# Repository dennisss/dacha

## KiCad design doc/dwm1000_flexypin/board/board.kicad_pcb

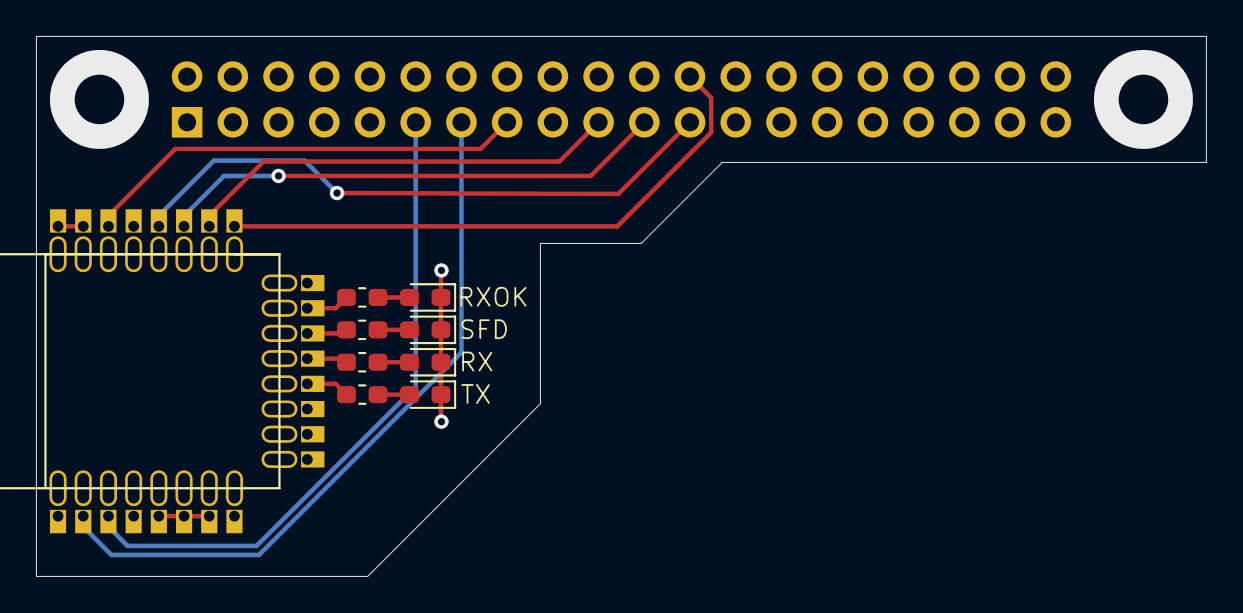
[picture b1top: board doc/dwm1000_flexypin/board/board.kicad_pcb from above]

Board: 4 copper layers, 65.0 x 30.0 mm, 12 parts (1 on the bottom side), 17 nets.

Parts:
D1, D2, D3, D4: LED; D_0603_1608Metric_Pad1.05x0.95mm_HandSolder
J1: DWM_LEFT; FlexyPin_1x08_P1.40mm
J2: DWM_RIGHT; FlexyPin_1x08_P1.40mm
J3: DWM_BOTTOM; FlexyPin_1x08_P1.40mm
J4: PI; PinSocket_2x20_P2.54mm_Vertical
R1, R2, R3, R4: 200; R_0603_1608Metric_Pad1.05x0.95mm_HandSolder

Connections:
+3V3: J1.5, J1.6, J1.7, J4.1, J4.17
GND: D1.1, D2.1, D3.1, D4.1, J1.8, J2.5, J2.7, J2.8, J3.8, J4.6, J4.9, J4.14, J4.20, J4.25, J4.30, J4.34, J4.39
IRQ: J2.6, J4.15
unnamed: D1.2, R1.2
unnamed: D2.2, R2.2
unnamed: D3.2, R3.2
unnamed: D4.2, R4.2
RSTN: J1.3, J4.11
RXLED: J3.5, R2.1
RXOKLED: J3.7, R4.1
SFDLED: J3.6, R3.1
SPICLK: J2.4, J4.23
SPICS: J2.1, J4.24
SPIMISO: J2.3, J4.21
SPIMOSI: J2.2, J4.19
TXLED: J3.4, R1.1
WAKEUP: J1.2, J4.13

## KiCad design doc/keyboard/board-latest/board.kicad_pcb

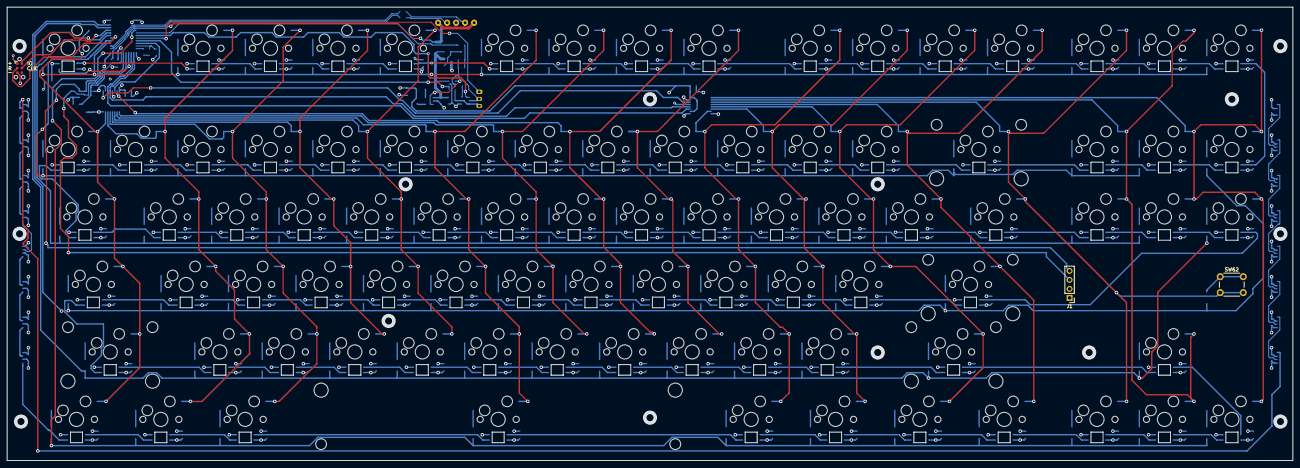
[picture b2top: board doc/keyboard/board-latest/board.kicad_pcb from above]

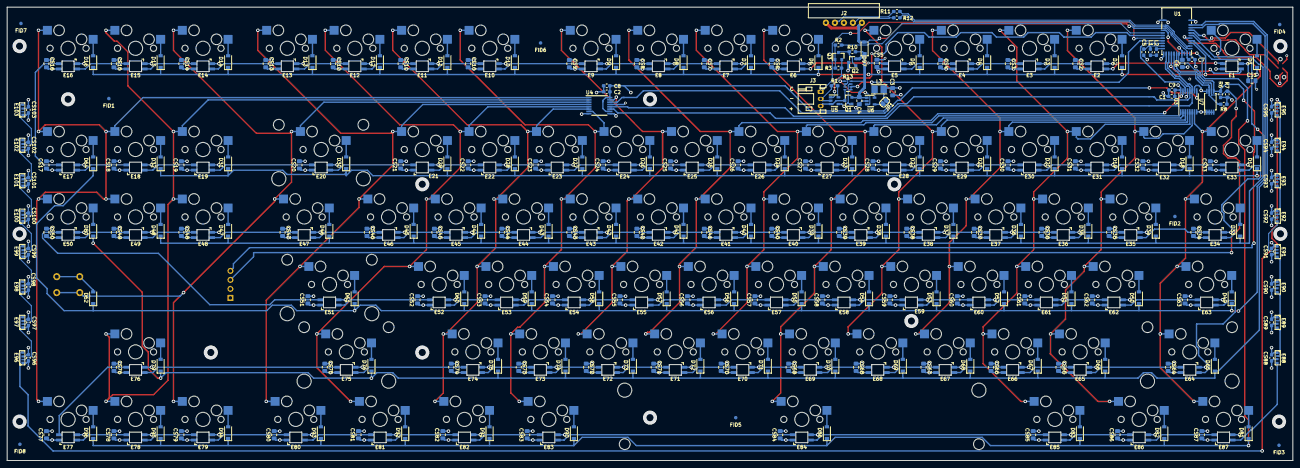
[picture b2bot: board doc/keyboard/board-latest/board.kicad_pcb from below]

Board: 4 copper layers, 363.0 x 128.0 mm, 427 parts (250 on the bottom side), 246 nets.

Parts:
C1, C2: 0.1uF; C_0603_1608Metric_Pad1.05x0.95mm_HandSolder
C3, C4, C6: 10uF; C_0805_2012Metric_Pad1.15x1.40mm_HandSolder
C5, C8, C9: 1uF; C_0603_1608Metric_Pad1.05x0.95mm_HandSolder
C7: 10uF; C_0603_1608Metric_Pad1.05x0.95mm_HandSolder
CS1, CS2, CS3, CS4, CS5, CS6, CS7, CS8, CS9, CS10, CS11, CS12, CS13, CS14, CS15, CS16, CS17, CS18, CS19, CS20, CS21, CS22, CS23, CS24, CS25, CS26, CS27, CS28, CS29, CS30, CS31, CS32, CS33, CS34, CS35, CS36, CS37, CS38, CS39, CS40, CS41, CS42, CS43, CS44, CS45, CS46, CS47, CS48, CS49, CS50, CS51, CS52, CS53, CS54, CS55, CS56, CS57, CS58, CS59, CS60, CS61, CS62, CS63, CS64, CS65, CS66, CS67, CS68, CS69, CS70, CS71, CS72, CS73, CS74, CS75, CS76, CS77, CS78, CS79, CS80, CS81, CS82, CS83, CS84, CS85, CS86, CS87: 0.1uF; C_0805_2012Metric_Pad1.15x1.40mm_HandSolder
CS88, CS89, CS90, CS91, CS92, CS93, CS94, CS95, CS96, CS97, CS98, CS99, CS100, CS101, CS102, CS103: 0.1uF; C_0603_1608Metric_Pad1.05x0.95mm_HandSolder
D1, D2, D3, D4, D5, D6, D7, D8, D9, D10, D11, D12, D13, D14, D15, D16, D17, D18, D19, D20, D21, D22, D23, D24, D25, D26, D27, D28, D29, D30, D31, D32, D33, D34, D35, D36, D37, D38, D39, D40, D41, D42, D43, D44, D45, D46, D47, D48, D49, D50, D51, D52, D53, D54, D55, D56, D57, D58, D59, D60, D61, D62, D64, D65, D66, D67, D68, D69, D70, D71, D72, D73, D74, D75, D76, D79, D80, D81, D82, D83, D86, D90, D91, D92, D93, D94, D95, D96: 1N4148W; D_SOD-123
D97: MBR120; D_SOD-123
E1, E2, E3, E4, E5, E6, E7, E8, E9, E10, E11, E12, E13, E14, E15, E16, E17, E18, E19, E20, E21, E22, E23, E24, E25, E26, E27, E28, E29, E30, E31, E32, E33, E34, E35, E36, E37, E38, E39, E40, E41, E42, E43, E44, E45, E46, E47, E48, E49, E50, E51, E52, E53, E54, E55, E56, E57, E58, E59, E60, E61, E62, E63, E64, E65, E66, E67, E68, E69, E70, E71, E72, E73, E74, E75, E76, E77, E78, E79, E80, E81, E82, E83, E84, E85, E86, E87: SK6812MINI-E; SK6812MINI-E-REV
E88, E89, E90, E91, E92, E93, E94, E95, E96, E97, E98, E99, E100, E101, E102, E103: SK6812MINI-E; SK6812B-SIDE
FID1, FID2, FID3, FID4, FID5, FID6, FID7, FID8: Fiducial; Fiducial_1mm_Mask2mm
J1: OLED; PinHeader_1x04_P2.54mm_Vertical
J2: Conn_01x05; ADAFRUIT_MAG_CONN_5_RIGHT
J3: Conn_01x03; JST_PH_S3B-PH-K_1x03_P2.00mm_Horizontal
J4: Conn_02x03_Odd_Even; Tag-Connect_TC2030-IDC-NL_2x03_P1.27mm_Vertical
JP1: Jumper_NC_Small; SolderJumper-2_P1.3mm_Open_RoundedPad1.0x1.5mm
L1: 15n; L_0603_1608Metric_Pad1.05x0.95mm_HandSolder
L2: 10u; L_0603_1608Metric_Pad1.05x0.95mm_HandSolder
L3: 2.2u; L_Taiyo-Yuden_NR-24xx_HandSoldering
Q1, Q2: DMG2305; SOT-23
Q3: 2N7002; SOT-23
R1: 4.7K; R_0603_1608Metric_Pad1.05x0.95mm_HandSolder
R2: 100; R_0603_1608Metric_Pad1.05x0.95mm_HandSolder
R3, R10: 100K; R_0603_1608Metric_Pad1.05x0.95mm_HandSolder
R6, R7: 2K; R_0603_1608Metric_Pad1.05x0.95mm_HandSolder
R8: 10K; R_0603_1608Metric_Pad1.05x0.95mm_HandSolder
R11, R12: 22; R_0603_1608Metric_Pad1.05x0.95mm_HandSolder
R13: 100K; R_Array_Concave_4x0603
SW1, SW2, SW3, SW4, SW5, SW6, SW7, SW8, SW9, SW10, SW11, SW12, SW13, SW14, SW15, SW16, SW17, SW18, SW19, SW20, SW21, SW22, SW23, SW24, SW25, SW26, SW27, SW28, SW29, SW31, SW32, SW34, SW35, SW36, SW37, SW38, SW39, SW40, SW41, SW42, SW43, SW44, SW45, SW47, SW48, SW50, SW51, SW52, SW53, SW54, SW55, SW56, SW57, SW58, SW59, SW60, SW64, SW66, SW67, SW68, SW69, SW70, SW71, SW72, SW73, SW74, SW75, SW79, SW80, SW94, SW95, SW96: SW_Push; MXOnly-1U-Hotswap
SW30: SW_Push; MXOnly-2U-Hotswap
SW33, SW46: SW_Push; MXOnly-1.5U-Hotswap
SW49: SW_Push; MXOnly-1.75U-Hotswap
SW61, SW65: SW_Push; MXOnly-2.25U-Hotswap
SW62: SW_Push; SW_PUSH_6mm
SW76: SW_Push; MXOnly-2.75U-Hotswap
SW81, SW82, SW83, SW90, SW91, SW92, SW93: SW_Push; MXOnly-1.25U-Hotswap
SW86: SW_Push; MXOnly-6.25U-Hotswap-ReversedStabilizers
U1: MDBT50-512K
U3, U4: 74HC595; TSSOP-16_4.4x5mm_P0.65mm
U5: MCP73831-2-OT; SOT-23-5
U6: LM3671-3.3; SOT-23-5
U7: 24LC256; TSSOP-8_4.4x3mm_P0.65mm

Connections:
+BATT: J3.3, Q1.3, R13.8, U5.3
BATTERY_CURRENT_COUNT: J3.1, U1.5
BATTERY_SCALED_V: R13.1, R13.2, U1.6
CHARGE_STAT: U1.4, U5.1
EEPROM_WP: R8.2, U1.14, U7.7
KEY_X1: SW1.2, SW17.2, SW33.2, SW49.2, SW65.2, SW81.2, U3.7
KEY_X2: SW2.2, SW18.2, SW34.2, SW50.2, SW66.2, SW82.2, U3.6
KEY_X3: SW3.2, SW19.2, SW35.2, SW51.2, SW67.2, SW83.2, U3.5
KEY_X4: SW4.2, SW20.2, SW36.2, SW52.2, SW68.2, U3.4
KEY_X5: SW5.2, SW21.2, SW37.2, SW53.2, SW69.2, U3.3
KEY_X6: SW6.2, SW22.2, SW38.2, SW54.2, SW70.2, SW86.2, U3.2
KEY_X7: SW7.2, SW23.2, SW39.2, SW55.2, SW71.2, U3.1
KEY_X8: SW8.2, SW24.2, SW40.2, SW56.2, SW72.2, U3.15
KEY_X9: SW9.2, SW25.2, SW41.2, SW57.2, SW73.2, U4.15
KEY_X10: SW10.2, SW26.2, SW42.2, SW58.2, SW74.2, SW90.2, U4.7
KEY_X11: SW11.2, SW27.2, SW43.2, SW59.2, SW75.2, SW91.2, U4.6
KEY_X12: SW12.2, SW28.2, SW44.2, SW60.2, SW76.2, SW92.2, U4.5
KEY_X13: SW13.2, SW29.2, SW45.2, SW61.2, SW93.2, U4.4
KEY_X14: SW14.2, SW30.2, SW46.2, SW62.2, SW94.2, U4.3
KEY_X15: SW15.2, SW31.2, SW47.2, SW79.2, SW95.2, U4.2
KEY_X16: SW16.2, SW32.2, SW48.2, SW64.2, SW80.2, SW96.2, U4.1
KEY_X_REGISTER_CLEAR: C1.2, C2.2, C3.2, C6.2, C8.2, C9.2, J1.2, J4.1, JP1.2, L3.2, R6.2, R7.2, R8.1, U1.17, U1.18, U3.10, U3.16, U4.10, U4.16, U7.8
KEY_X_REGISTER_CLK: U1.11, U3.12, U4.12
KEY_X_REGISTER_ENABLE: C1.1, C2.1, C3.1, C4.1, C5.2, C6.1, C7.2, C8.1, C9.1, CS1.1, CS2.1, CS3.1, CS4.1, CS5.1, CS6.1, CS7.1, CS8.1, CS9.1, CS10.1, CS11.1, CS12.1, CS13.1, CS14.1, CS15.1, CS16.1, CS17.1, CS18.1, CS19.1, CS20.1, CS21.1, CS22.1, CS23.1, CS24.1, CS25.1, CS26.1, CS27.1, CS28.1, CS29.1, CS30.1, CS31.1, CS32.1, CS33.1, CS34.1, CS35.1, CS36.1, CS37.1, CS38.1, CS39.1, CS40.1, CS41.1, CS42.1, CS43.1, CS44.1, CS45.1, CS46.1, CS47.1, CS48.1, CS49.1, CS50.1, CS51.1, CS52.1, CS53.1, CS54.1, CS55.1, CS56.1, CS57.1, CS58.1, CS59.1, CS60.1, CS61.1, CS62.1, CS63.1, CS64.1, CS65.1, CS66.1, CS67.1, CS68.1, CS69.1, CS70.1, CS71.1, CS72.1, CS73.1, CS74.1, CS75.1, CS76.1, CS77.1, CS78.1, CS79.1, CS80.1, CS81.1, CS82.1, CS83.1, CS84.1, CS85.1, CS86.1, CS87.1, CS88.1, CS89.1, CS90.1, CS91.1, CS92.1, CS93.1, CS94.1, CS95.1, CS96.1, CS97.1, CS98.1, CS99.1, CS100.1, CS101.1, CS102.1, CS103.1, E1.3, E2.3, E3.3, E4.3, E5.3, E6.3, E7.3, E8.3, E9.3, E10.3, E11.3, E12.3, E13.3, E14.3, E15.3, E16.3, E17.3, E18.3, E19.3, E20.3, E21.3, E22.3, E23.3, E24.3, E25.3, E26.3, E27.3, E28.3, E29.3, E30.3, E31.3, E32.3, E33.3, E34.3, E35.3, E36.3, E37.3, E38.3, E39.3, E40.3, E41.3, E42.3, E43.3, E44.3, E45.3, E46.3, E47.3, E48.3, E49.3, E50.3, E51.3, E52.3, E53.3, E54.3, E55.3, E56.3, E57.3, E58.3, E59.3, E60.3, E61.3, E62.3, E63.3, E64.3, E65.3, E66.3, E67.3, E68.3, E69.3, E70.3, E71.3, E72.3, E73.3, E74.3, E75.3, E76.3, E77.3, E78.3, E79.3, E80.3, E81.3, E82.3, E83.3, E84.3, E85.3, E86.3, E87.3, E88.3, E89.3, E90.3, E91.3, E92.3, E93.3, E94.3, E95.3, E96.3, E97.3, E98.3, E99.3, E100.3, E101.3, E102.3, E103.3, J1.1, J2.3, J3.2, J4.5, Q3.2, R1.1, R3.2, R13.6, R13.7, U1.1, U1.10, U1.20, U1.31, U3.8, U3.13, U4.8, U4.9, U4.13, U5.2, U6.2, U7.1, U7.2, U7.3, U7.4
KEY_X_SERIAL_CLK: U1.12, U3.11, U4.11
KEY_X_SERIAL_DATA: U1.7, U3.14
KEY_Y1: D1.1, D2.1, D3.1, D4.1, D5.1, D6.1, D7.1, D8.1, D9.1, D10.1, D11.1, D12.1, D13.1, D14.1, D15.1, D16.1, U1.23
KEY_Y2: D17.1, D18.1, D19.1, D20.1, D21.1, D22.1, D23.1, D24.1, D25.1, D26.1, D27.1, D28.1, D29.1, D30.1, D31.1, D32.1, U1.24
KEY_Y3: D33.1, D34.1, D35.1, D36.1, D37.1, D38.1, D39.1, D40.1, D41.1, D42.1, D43.1, D44.1, D45.1, D46.1, D47.1, D48.1, U1.26
KEY_Y4: D49.1, D50.1, D51.1, D52.1, D53.1, D54.1, D55.1, D56.1, D57.1, D58.1, D59.1, D60.1, D61.1, D62.1, D64.1, U1.29
KEY_Y5: D65.1, D66.1, D67.1, D68.1, D69.1, D70.1, D71.1, D72.1, D73.1, D74.1, D75.1, D76.1, D79.1, D80.1, U1.30
KEY_Y6: D81.1, D82.1, D83.1, D86.1, D90.1, D91.1, D92.1, D93.1, D94.1, D95.1, D96.1, U1.2
LED_ENABLE: R2.2, U1.3
LED_SERIAL: E1.4, U1.13
LED_SERIAL_1: E11.2, E12.4
LED_SERIAL_2: E22.2, E23.4
LED_SERIAL_3: E33.2, E34.4
LED_SERIAL_4: E44.2, E45.4
LED_SERIAL_5: E55.2, E56.4
LED_SERIAL_6: E66.2, E67.4
LED_SERIAL_7: E77.2, E78.4
LED_SERIAL_8: E87.2, E88.4
LED_VDD: CS1.2, CS2.2, CS3.2, CS4.2, CS5.2, CS6.2, CS7.2, CS8.2, CS9.2, CS10.2, CS11.2, CS12.2, CS13.2, CS14.2, CS15.2, CS16.2, CS17.2, CS18.2, CS19.2, CS20.2, CS21.2, CS22.2, CS23.2, CS24.2, CS25.2, CS26.2, CS27.2, CS28.2, CS29.2, CS30.2, CS31.2, CS32.2, CS33.2, CS34.2, CS35.2, CS36.2, CS37.2, CS38.2, CS39.2, CS40.2, CS41.2, CS42.2, CS43.2, CS44.2, CS45.2, CS46.2, CS47.2, CS48.2, CS49.2, CS50.2, CS51.2, CS52.2, CS53.2, CS54.2, CS55.2, CS56.2, CS57.2, CS58.2, CS59.2, CS60.2, CS61.2, CS62.2, CS63.2, CS64.2, CS65.2, CS66.2, CS67.2, CS68.2, CS69.2, CS70.2, CS71.2, CS72.2, CS73.2, CS74.2, CS75.2, CS76.2, CS77.2, CS78.2, CS79.2, CS80.2, CS81.2, CS82.2, CS83.2, CS84.2, CS85.2, CS86.2, CS87.2, CS88.2, CS89.2, CS90.2, CS91.2, CS92.2, CS93.2, CS94.2, CS95.2, CS96.2, CS97.2, CS98.2, CS99.2, CS100.2, CS101.2, CS102.2, CS103.2, E1.1, E2.1, E3.1, E4.1, E5.1, E6.1, E7.1, E8.1, E9.1, E10.1, E11.1, E12.1, E13.1, E14.1, E15.1, E16.1, E17.1, E18.1, E19.1, E20.1, E21.1, E22.1, E23.1, E24.1, E25.1, E26.1, E27.1, E28.1, E29.1, E30.1, E31.1, E32.1, E33.1, E34.1, E35.1, E36.1, E37.1, E38.1, E39.1, E40.1, E41.1, E42.1, E43.1, E44.1, E45.1, E46.1, E47.1, E48.1, E49.1, E50.1, E51.1, E52.1, E53.1, E54.1, E55.1, E56.1, E57.1, E58.1, E59.1, E60.1, E61.1, E62.1, E63.1, E64.1, E65.1, E66.1, E67.1, E68.1, E69.1, E70.1, E71.1, E72.1, E73.1, E74.1, E75.1, E76.1, E77.1, E78.1, E79.1, E80.1, E81.1, E82.1, E83.1, E84.1, E85.1, E86.1, E87.1, E88.1, E89.1, E90.1, E91.1, E92.1, E93.1, E94.1, E95.1, E96.1, E97.1, E98.1, E99.1, E100.1, E101.1, E102.1, E103.1, Q2.3
unnamed: C5.1, L1.1, U1.8
unnamed: D1.2, SW1.1
unnamed: D2.2, SW2.1
unnamed: D3.2, SW3.1
unnamed: D4.2, SW4.1
unnamed: D5.2, SW5.1
unnamed: D6.2, SW6.1
unnamed: D7.2, SW7.1
unnamed: D8.2, SW8.1
unnamed: D9.2, SW9.1
unnamed: D10.2, SW10.1
unnamed: D11.2, SW11.1
unnamed: D12.2, SW12.1
unnamed: D13.2, SW13.1
unnamed: D14.2, SW14.1
unnamed: D15.2, SW15.1
unnamed: D16.2, SW16.1
unnamed: D17.2, SW17.1
unnamed: D18.2, SW18.1
unnamed: D19.2, SW19.1
unnamed: D20.2, SW20.1
unnamed: D21.2, SW21.1
unnamed: D22.2, SW22.1
unnamed: D23.2, SW23.1
unnamed: D24.2, SW24.1
unnamed: D25.2, SW25.1
unnamed: D26.2, SW26.1
unnamed: D27.2, SW27.1
unnamed: D28.2, SW28.1
unnamed: D29.2, SW29.1
unnamed: D30.2, SW30.1
unnamed: D31.2, SW31.1
unnamed: D32.2, SW32.1
unnamed: D33.2, SW33.1
unnamed: D34.2, SW34.1
unnamed: D35.2, SW35.1
unnamed: D36.2, SW36.1
unnamed: D37.2, SW37.1
unnamed: D38.2, SW38.1
unnamed: D39.2, SW39.1
unnamed: D40.2, SW40.1
unnamed: D41.2, SW41.1
unnamed: D42.2, SW42.1
unnamed: D43.2, SW43.1
unnamed: D44.2, SW44.1
unnamed: D45.2, SW45.1
unnamed: D46.2, SW46.1
unnamed: D47.2, SW47.1
unnamed: D48.2, SW48.1
unnamed: D49.2, SW49.1
unnamed: D50.2, SW50.1
unnamed: D51.2, SW51.1
unnamed: D52.2, SW52.1
unnamed: D53.2, SW53.1
unnamed: D54.2, SW54.1
unnamed: D55.2, SW55.1
unnamed: D56.2, SW56.1
unnamed: D57.2, SW57.1
unnamed: D58.2, SW58.1
unnamed: D59.2, SW59.1
unnamed: D60.2, SW60.1
unnamed: D61.2, SW61.1
unnamed: D62.2, SW62.1
unnamed: D64.2, SW64.1
unnamed: D65.2, SW65.1
unnamed: D66.2, SW66.1
unnamed: D67.2, SW67.1
unnamed: D68.2, SW68.1
unnamed: D69.2, SW69.1
unnamed: D70.2, SW70.1
unnamed: D71.2, SW71.1
unnamed: D72.2, SW72.1
unnamed: D73.2, SW73.1
unnamed: D74.2, SW74.1
unnamed: D75.2, SW75.1
unnamed: D76.2, SW76.1
unnamed: D79.2, SW79.1
unnamed: D80.2, SW80.1
unnamed: D81.2, SW81.1
unnamed: D82.2, SW82.1
unnamed: D83.2, SW83.1
unnamed: D86.2, SW86.1
unnamed: D90.2, SW90.1
unnamed: D91.2, SW91.1
unnamed: D92.2, SW92.1
unnamed: D93.2, SW93.1
unnamed: D94.2, SW94.1
unnamed: D95.2, SW95.1
unnamed: D96.2, SW96.1
unnamed: E1.2, E2.4
unnamed: E2.2, E3.4
unnamed: E3.2, E4.4
unnamed: E4.2, E5.4
unnamed: E5.2, E6.4
unnamed: E6.2, E7.4
unnamed: E7.2, E8.4
unnamed: E8.2, E9.4
unnamed: E10.2, E11.4
unnamed: E9.2, E10.4
unnamed: E12.2, E13.4
unnamed: E13.2, E14.4
unnamed: E14.2, E15.4
unnamed: E15.2, E16.4
unnamed: E16.2, E17.4
unnamed: E17.2, E18.4
unnamed: E18.2, E19.4
unnamed: E19.2, E20.4
unnamed: E20.2, E21.4
unnamed: E21.2, E22.4
unnamed: E23.2, E24.4
unnamed: E24.2, E25.4
unnamed: E25.2, E26.4
unnamed: E26.2, E27.4
unnamed: E27.2, E28.4
unnamed: E28.2, E29.4
unnamed: E29.2, E30.4
unnamed: E30.2, E31.4
unnamed: E31.2, E32.4
unnamed: E32.2, E33.4
unnamed: E34.2, E35.4
unnamed: E35.2, E36.4
unnamed: E36.2, E37.4
unnamed: E37.2, E38.4
unnamed: E38.2, E39.4
unnamed: E39.2, E40.4
unnamed: E40.2, E41.4
unnamed: E41.2, E42.4
unnamed: E42.2, E43.4
unnamed: E43.2, E44.4
unnamed: E45.2, E46.4
unnamed: E46.2, E47.4
unnamed: E47.2, E48.4
unnamed: E48.2, E49.4
unnamed: E49.2, E50.4
unnamed: E50.2, E51.4
unnamed: E51.2, E52.4
unnamed: E52.2, E53.4
unnamed: E53.2, E54.4
unnamed: E54.2, E55.4
unnamed: E56.2, E57.4
unnamed: E57.2, E58.4
unnamed: E58.2, E59.4
unnamed: E59.2, E60.4
unnamed: E60.2, E61.4
unnamed: E61.2, E62.4
unnamed: E62.2, E63.4
unnamed: E63.2, E64.4
unnamed: E64.2, E65.4
unnamed: E65.2, E66.4
unnamed: E67.2, E68.4
unnamed: E68.2, E69.4
unnamed: E69.2, E70.4
unnamed: E70.2, E71.4
unnamed: E71.2, E72.4
unnamed: E72.2, E73.4
unnamed: E73.2, E74.4
unnamed: E74.2, E75.4
unnamed: E75.2, E76.4
unnamed: E76.2, E77.4
unnamed: E78.2, E79.4
unnamed: E79.2, E80.4
unnamed: E80.2, E81.4
unnamed: E81.2, E82.4
unnamed: E82.2, E83.4
unnamed: E83.2, E84.4
unnamed: E84.2, E85.4
unnamed: E85.2, E86.4
unnamed: E86.2, E87.4
unnamed: E88.2, E89.4
unnamed: E89.2, E90.4
unnamed: E90.2, E91.4
unnamed: E91.2, E92.4
unnamed: E92.2, E93.4
unnamed: E93.2, E94.4
unnamed: E94.2, E95.4
unnamed: E95.2, E96.4
unnamed: E96.2, E97.4
unnamed: E97.2, E98.4
unnamed: E98.2, E99.4
unnamed: E100.2, E101.4
unnamed: E99.2, E100.4
unnamed: E101.2, E102.4
unnamed: E102.2, E103.4
unnamed: JP1.1, U6.4
unnamed: L1.2, L2.1
unnamed: L2.2, U1.9
unnamed: L3.1, U6.5
unnamed: Q2.1, Q3.3, R10.2
unnamed: Q3.1, R2.1, R3.1
unnamed: R1.2, U5.5
unnamed: R13.5, U6.3
unnamed: U3.9, U4.14
RESET: J4.3, U1.25
SCL: J1.3, R7.1, U1.15, U7.6
SDA: J1.4, R6.1, U1.16, U7.5
SWDCLK: J4.4, U1.28
SWDIO: J4.2, U1.27
USB_D+: R11.2, U1.22
USB_D-: R12.1, U1.21
USB_RAW_D+: J2.2, R11.1
USB_RAW_D-: J2.4, R12.2
VBUS: C7.1, D97.2, J2.1, J2.5, Q1.1, R13.3, U1.19, U5.4
VHIGH: C4.2, D97.1, Q1.2, Q2.2, R10.1, R13.4, U6.1

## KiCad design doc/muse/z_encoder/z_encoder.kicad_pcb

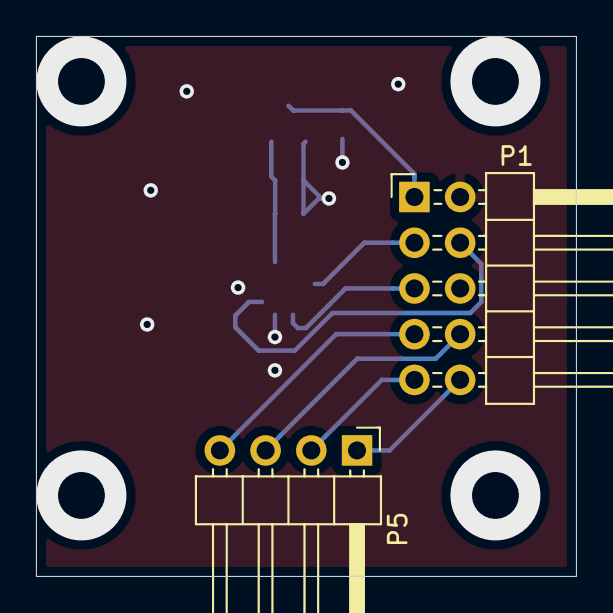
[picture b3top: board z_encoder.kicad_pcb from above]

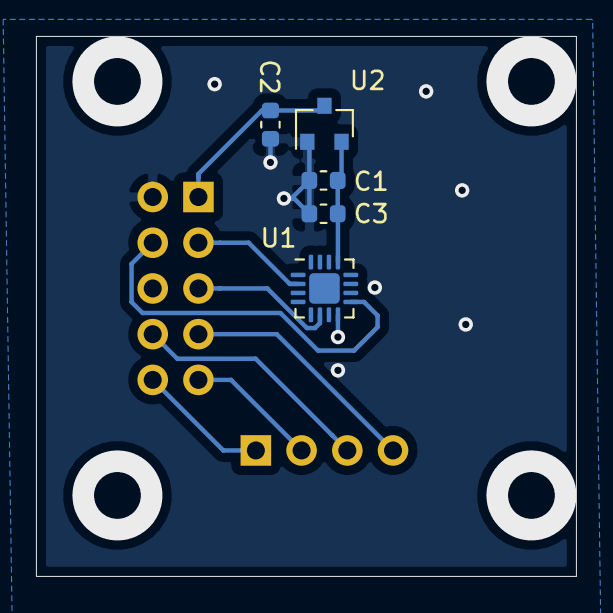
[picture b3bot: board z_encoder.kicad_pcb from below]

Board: 2 copper layers, 30.0 x 30.0 mm, 7 parts (5 on the bottom side), 10 nets.

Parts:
C1: 0u1; C_0603_1608Metric
C2, C3: 1u; C_0603_1608Metric
P1: Conn_02x05_Odd_Even; PinHeader_2x05_P2.54mm_Horizontal
P5: Conn_01x04; PinHeader_1x04_P2.54mm_Horizontal
U1: MA730GQ-P; QFN-16-1EP_3x3mm_P0.5mm_EP1.7x1.7mm
U2: AP2127N-3.3; SOT-23

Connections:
+3V3: C1.1, C3.1, U1.13, U2.2
+5V: C2.1, P1.1, U2.3
AUX_1: P1.10, P5.1
AUX_2: P1.9, P5.2
AUX_3: P1.8, P5.3
AUX_4: P1.7, P5.4
GND: C1.2, C2.2, C3.2, P1.2, U1.8, U2.1
MAG_A: P1.3, U1.2
MAG_B: P1.5, U1.6
MAG_PWM: P1.4, U1.9

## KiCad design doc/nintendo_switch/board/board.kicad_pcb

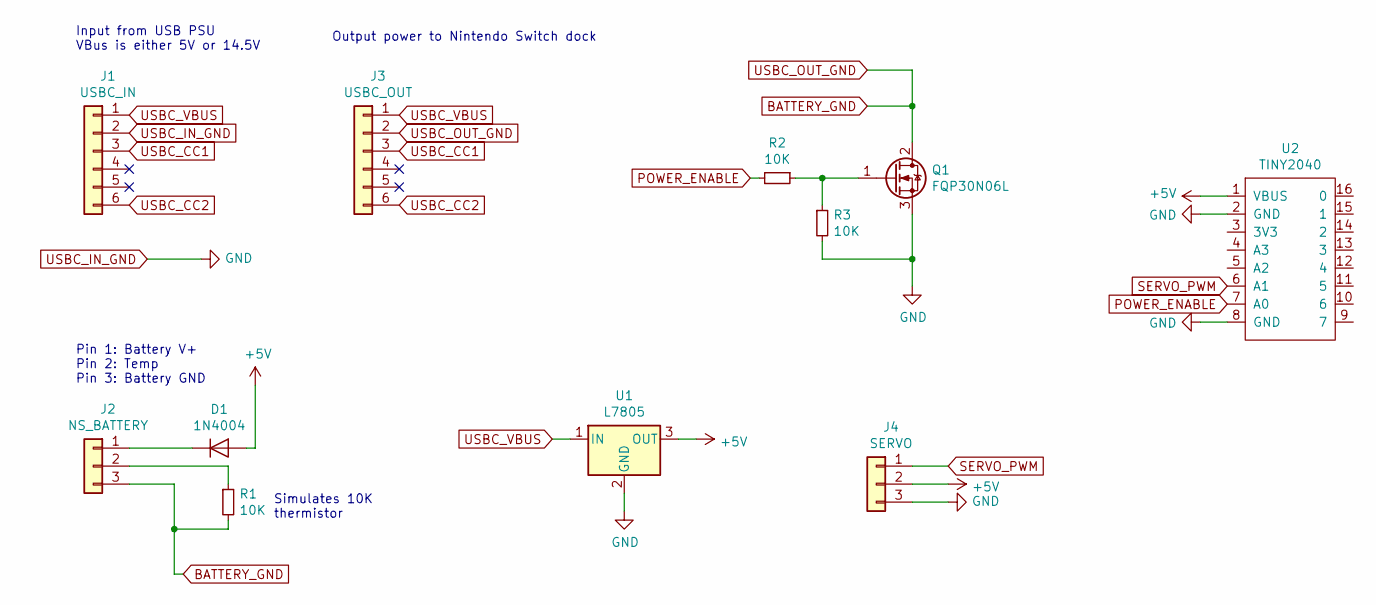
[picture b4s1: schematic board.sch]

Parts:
D1: 1N4004; D_DO-41_SOD81_P10.16mm_Horizontal
J1: USBC_IN; USB_C_BREAKOUT
J2: NS_BATTERY; PinHeader_1x03_P2.54mm_Vertical
J3: USBC_OUT; USB_C_BREAKOUT
J4: SERVO; PinHeader_1x03_P2.54mm_Vertical
Q1: FQP30N06L; TO-220-3_Vertical
R1, R2, R3: 10K; R_Axial_DIN0309_L9.0mm_D3.2mm_P12.70mm_Horizontal
U1: L7805; TO-220-3_Vertical
U2: TINY2040; TINY2040_TH

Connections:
+5V: D1.2 (A), J4.2, U1.3 (OUT), U2.1 (VBUS)
BATTERY_GND: J2.3, J3.2, Q1.2 (D), R1.2
unnamed: D1.1 (K), J2.1
unnamed: J2.2, R1.1
unnamed: Q1.1 (G), R2.1, R3.1
POWER_ENABLE: R2.2, U2.7 (A0)
SERVO_PWM: J4.1, U2.6 (A1)
USBC_CC1: J1.3, J3.3
USBC_CC2: J1.6, J3.6
USBC_IN_GND: J1.2, J4.3, Q1.3 (S), R3.2, U1.2 (GND), U2.2 (GND), U2.8 (GND)
USBC_VBUS: J1.1, J3.1, U1.1 (IN)

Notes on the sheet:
Pin 1: Battery V+ Pin 2: Temp Pin 3: Battery GND
Input from USB PSU VBus is either 5V or 14.5V
Output power to Nintendo Switch dock
Simulates 10K thermistor

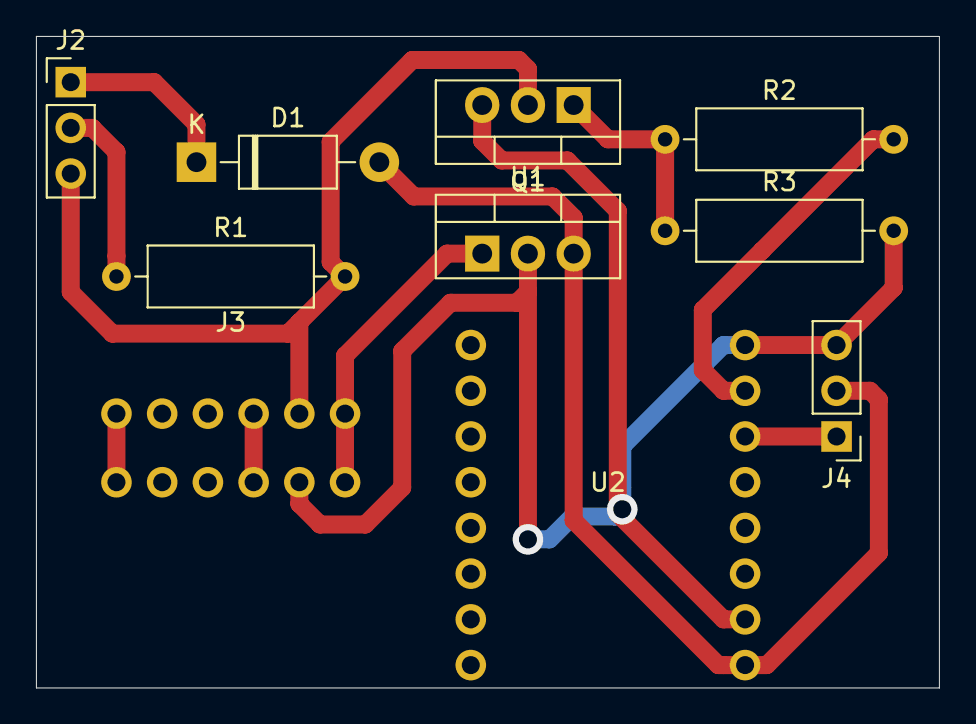
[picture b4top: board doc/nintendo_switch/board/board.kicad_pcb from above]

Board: 2 copper layers, 50.2 x 36.2 mm, 11 parts (1 on the bottom side), 11 nets.

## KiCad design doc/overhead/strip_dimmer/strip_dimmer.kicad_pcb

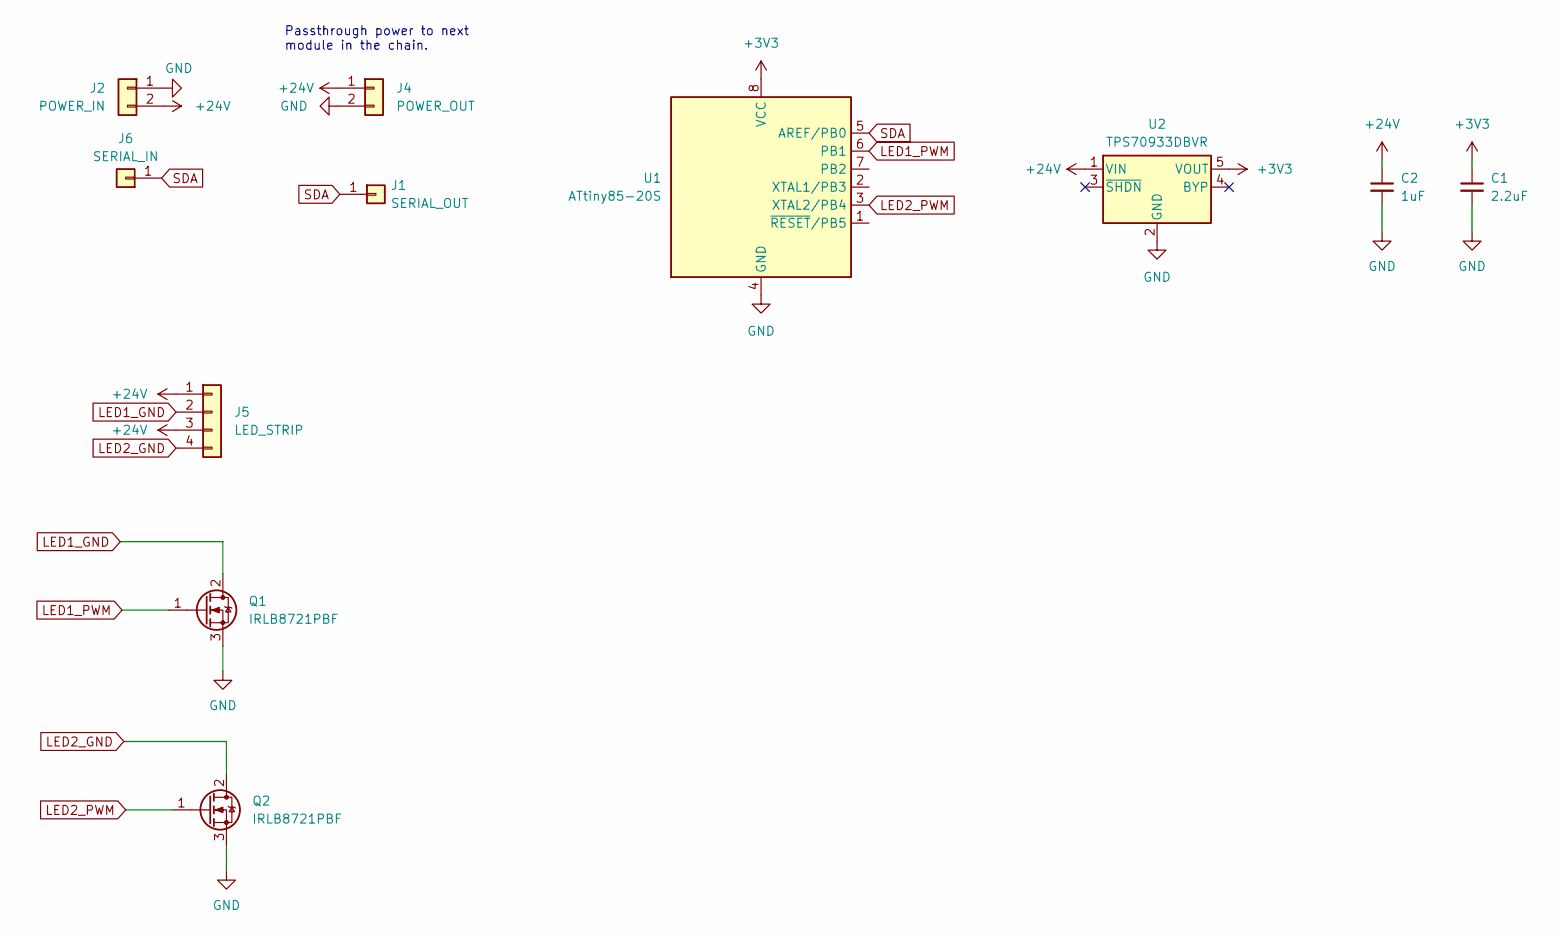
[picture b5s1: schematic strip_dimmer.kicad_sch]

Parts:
C1: 2.2uF; C_0805_2012Metric_Pad1.18x1.45mm_HandSolder
C2: 1uF; C_0805_2012Metric_Pad1.18x1.45mm_HandSolder
J1: SERIAL_OUT; PinHeader_1x01_P2.54mm_Horizontal
J2: POWER_IN; TerminalBlock_RND_205-00001_1x02_P5.00mm_Horizontal
J4: POWER_OUT; TerminalBlock_RND_205-00001_1x02_P5.00mm_Horizontal
J5: LED_STRIP; TerminalBlock_RND_205-00003_1x04_P5.00mm_Horizontal
J6: SERIAL_IN; PinHeader_1x01_P2.54mm_Horizontal
Q1, Q2: IRLB8721PBF; TO-220-3_Vertical
U1: ATtiny85-20S; SOIC-8W_5.3x5.3mm_P1.27mm
U2: TPS70933DBVR; SOT-23-5_HandSoldering

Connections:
+3V3: C1.1, U1.8 (VCC), U2.5 (VOUT)
+24V: C2.1, J2.2, J4.1, J5.1, J5.3, U2.1 (VIN)
GND: C1.2, C2.2, J2.1, J4.2, Q1.3 (S), Q2.3 (S), U1.4 (GND), U2.2 (GND)
LED1_GND: J5.2, Q1.2 (D)
LED1_PWM: Q1.1 (G), U1.6 (PB1)
LED2_GND: J5.4, Q2.2 (D)
LED2_PWM: Q2.1 (G), U1.3 (XTAL2/PB4)
SDA: J1.1, J6.1, U1.5 (AREF/PB0)

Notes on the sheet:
Passthrough power to next module in the chain.

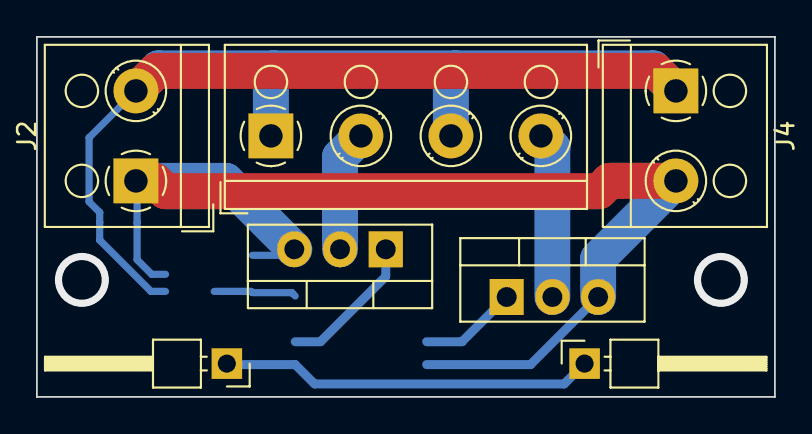
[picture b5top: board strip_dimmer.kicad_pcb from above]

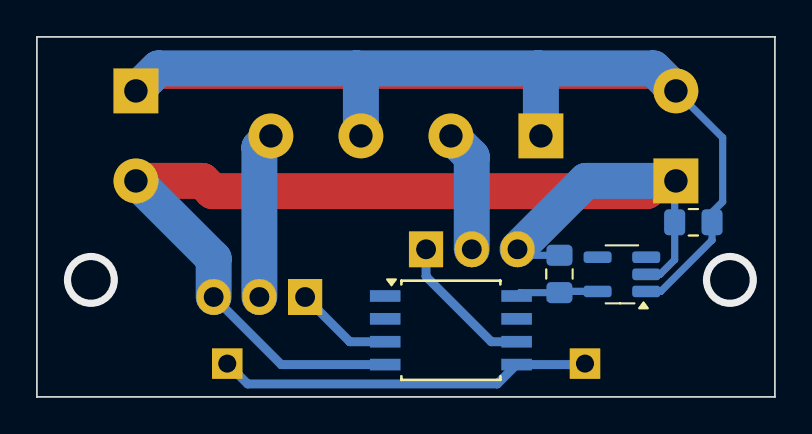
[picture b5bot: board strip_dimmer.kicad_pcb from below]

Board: 2 copper layers, 41.0 x 20.0 mm, 11 parts (4 on the bottom side), 8 nets.
